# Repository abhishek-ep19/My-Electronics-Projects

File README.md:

# Student Researched And Developed(SRAD) RF Transceiver
This is a project on design of a SRAD RF Transceiver which was made as a part of avionics team,Sounding Rocket, IIT Madras. This was designed using nRF905 RFIC and uses SPI AND I2C protocol. It operates on frequency 433 MHz which is operable in United States. Due to its low frequency we would be able to use an optimal length of antenna for communication at large distances and 10000 ft. at which rocket will attain its maximum height is well in its range above the ground.
This was made using Autodesk EAGLE and contains the borad design and schematics. Along with it this repository also contains nRF905 RFIC manual.

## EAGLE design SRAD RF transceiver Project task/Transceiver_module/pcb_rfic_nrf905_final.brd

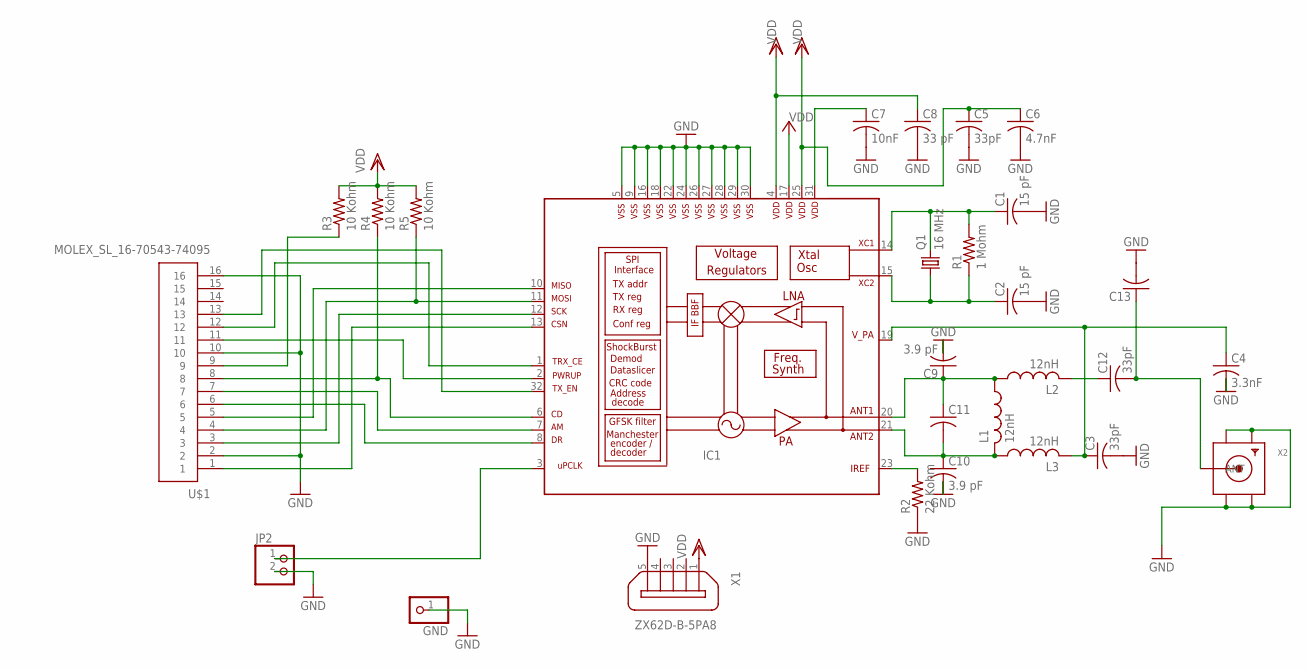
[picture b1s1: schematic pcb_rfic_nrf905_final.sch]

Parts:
C1, C2: 15 pF; C0603; MPN MCMT18N150F500CT
C3, C5, C12: 33pF; C0603; MPN MCMT18N330F100CT
C4: 3.3nF; C0603; MPN C0603C332J5JACTU
C6: 4.7nF; C0603; MPN C0603X472K5RAC3316
C7: 10nF; C0603; MPN CGA3E2C0G1H103J080AA
C8: 33 pF; C0603; MPN C0603C330J5GACTU
C9, C10: 3.9 pF; C0603; MPN 06035A3R9DAT2A
C11, C13: C-USC0603; C0603
GND: PINHD-1X1; 1X01; MPN VO615A-1X019T
IC1: NRF905; LQFP-32
JP2: PINHD-1X2; 1X02
L1, L2, L3: 12nH; 0204V; MPN MCFT000084
Q1: 16 MHz; HC18U-V
R1: 1 Mohm; R0603; MPN MCWR06X1004FTL
R2: 22 Kohm; R0603
R3, R4, R5: 10 Kohm; R0603
U$1: MOLEX_SL_16-70543-74095; SL_70543_16
X1: ZX62D-B-5PA8
X2: SMACONNECTOR_EDGE; SMA_EDGELAUNCH

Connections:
GND: C1.2, C2.2, C3.2, C4.2, C5.2, C6.2, C7.2, C8.2, C9.2, C10.2, C13.2, GND.1, IC1.5 (VSS5), IC1.9 (VSS9), IC1.16 (VSS16), IC1.18 (VSS18), IC1.22 (VSS22), IC1.24 (VSS24), IC1.26 (VSS26), IC1.27 (VSS27), IC1.28 (VSS28), IC1.29 (VSS29), IC1.30 (VSS30), JP2.2, R2.1, U$1.2, U$1.10, U$1.16, X1.5, X2.GND@1 (GND4), X2.GND@2 (GND3), X2.GND@3 (GND2), X2.GND@4 (GND1)
unnamed: C1.1, IC1.14 (XC1), Q1.2, R1.2
unnamed: C2.1, IC1.15 (XC2), Q1.1, R1.1
unnamed: IC1.23 (IREF), R2.2
unnamed: C7.1, IC1.31 (DVDD1V2)
unnamed: C9.1, C11.1, IC1.20 (ANT1), L1.1, L2.1
unnamed: C10.1, C11.2, IC1.21 (ANT2), L1.2, L3.1
unnamed: C12.1, L2.2
unnamed: C3.1, C4.1, IC1.19 (VDD_PA), L3.2
unnamed: IC1.10 (MISO), U$1.5
unnamed: IC1.11 (MOSI), R5.1, U$1.4
unnamed: IC1.12 (SCK), U$1.3
unnamed: R3.1, U$1.9
unnamed: IC1.1 (TRX_CE), U$1.12
unnamed: IC1.2 (PWR_UP), U$1.11
unnamed: IC1.32 (TX_EN), U$1.13
unnamed: IC1.6 (CD), R4.1, U$1.8
unnamed: IC1.7 (AM), U$1.7
unnamed: IC1.8 (DR), U$1.6
unnamed: IC1.3 (UPCLK), JP2.1
unnamed: IC1.13 (CSN), U$1.1
unnamed: C12.2, C13.1, X2.P (ANT)
VCC: IC1.17 (VDD17)
VDD: C5.1, C6.1, C8.1, IC1.4 (VDD4), IC1.25 (VDD25), R3.2, R4.2, R5.2, X1.1

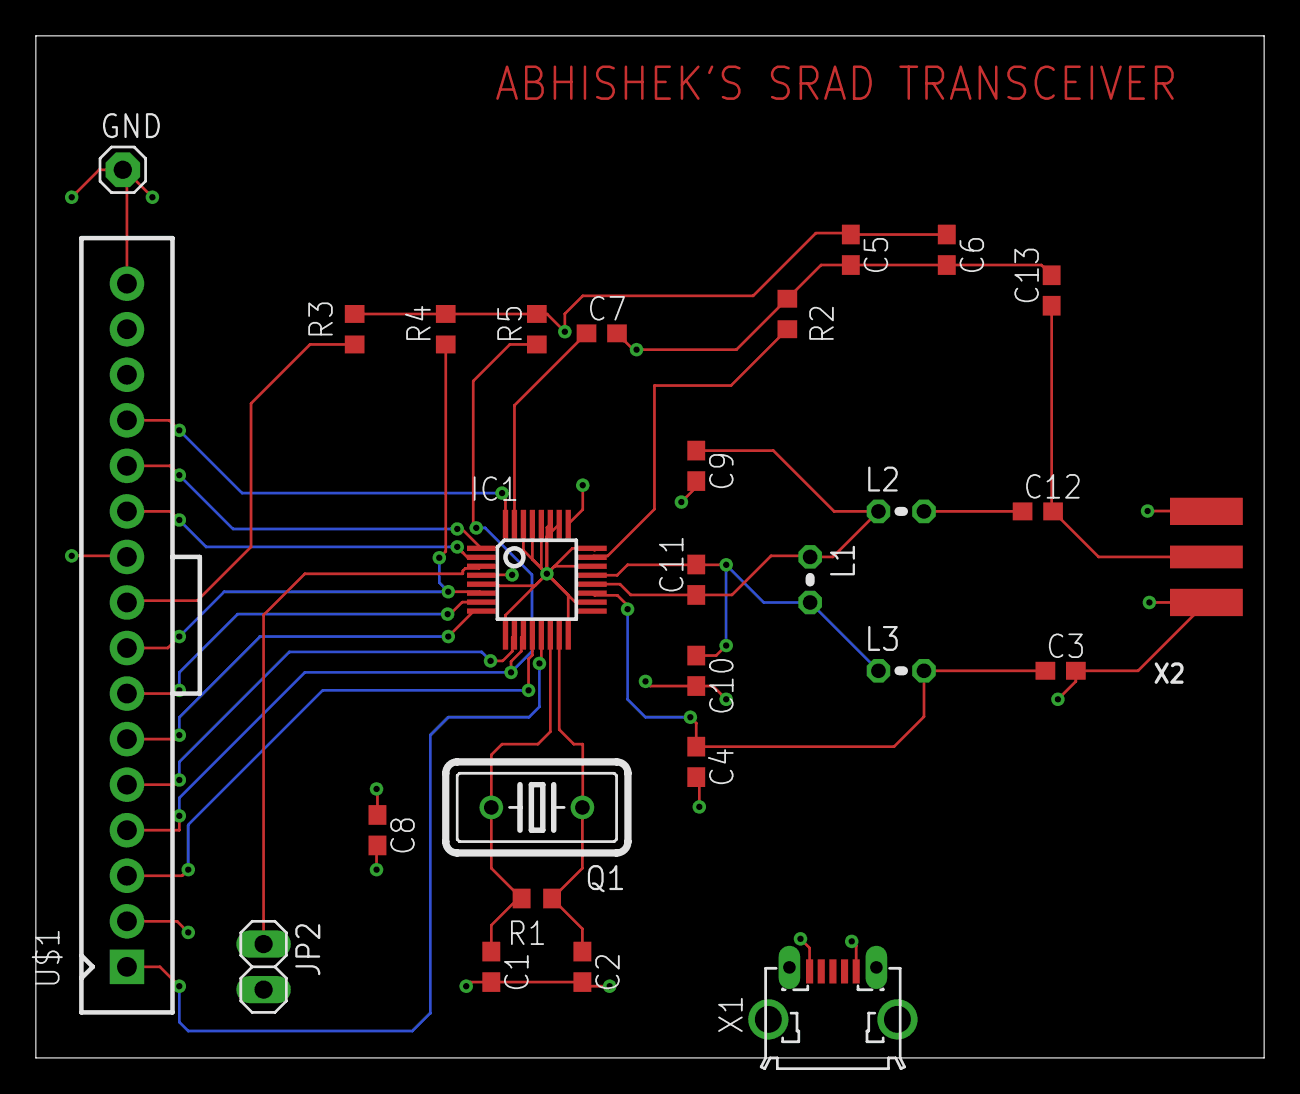
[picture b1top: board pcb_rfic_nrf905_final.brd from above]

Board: 4 copper layers, 68.5 x 57.0 mm, 28 parts (0 on the bottom side), 23 nets.
